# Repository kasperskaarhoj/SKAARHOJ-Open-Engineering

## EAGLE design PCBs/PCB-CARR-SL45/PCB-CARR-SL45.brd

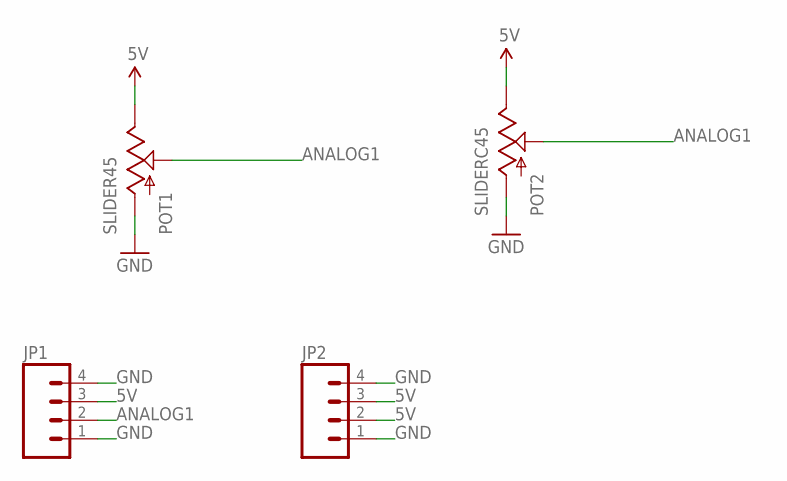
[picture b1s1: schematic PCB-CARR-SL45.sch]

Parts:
JP1, JP2: M04PTH; 1X04
POT1: SLIDER45
POT2: SLIDERC45; SLIDER45-CAR1

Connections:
5V: JP1.3, JP2.2, JP2.3, POT1.1 (E), POT2.1 (E)
ANALOG1: JP1.2, POT1.2A (S), POT2.2A (S)
GND: JP1.1, JP1.4, JP2.1, JP2.4, POT1.3 (A), POT2.3 (A)

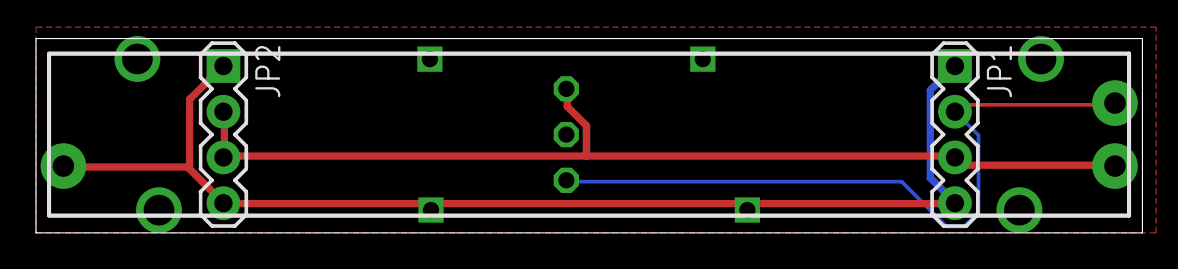
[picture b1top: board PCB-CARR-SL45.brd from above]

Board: 2 copper layers, 61.5 x 10.8 mm, 4 parts (0 on the bottom side), 3 nets.

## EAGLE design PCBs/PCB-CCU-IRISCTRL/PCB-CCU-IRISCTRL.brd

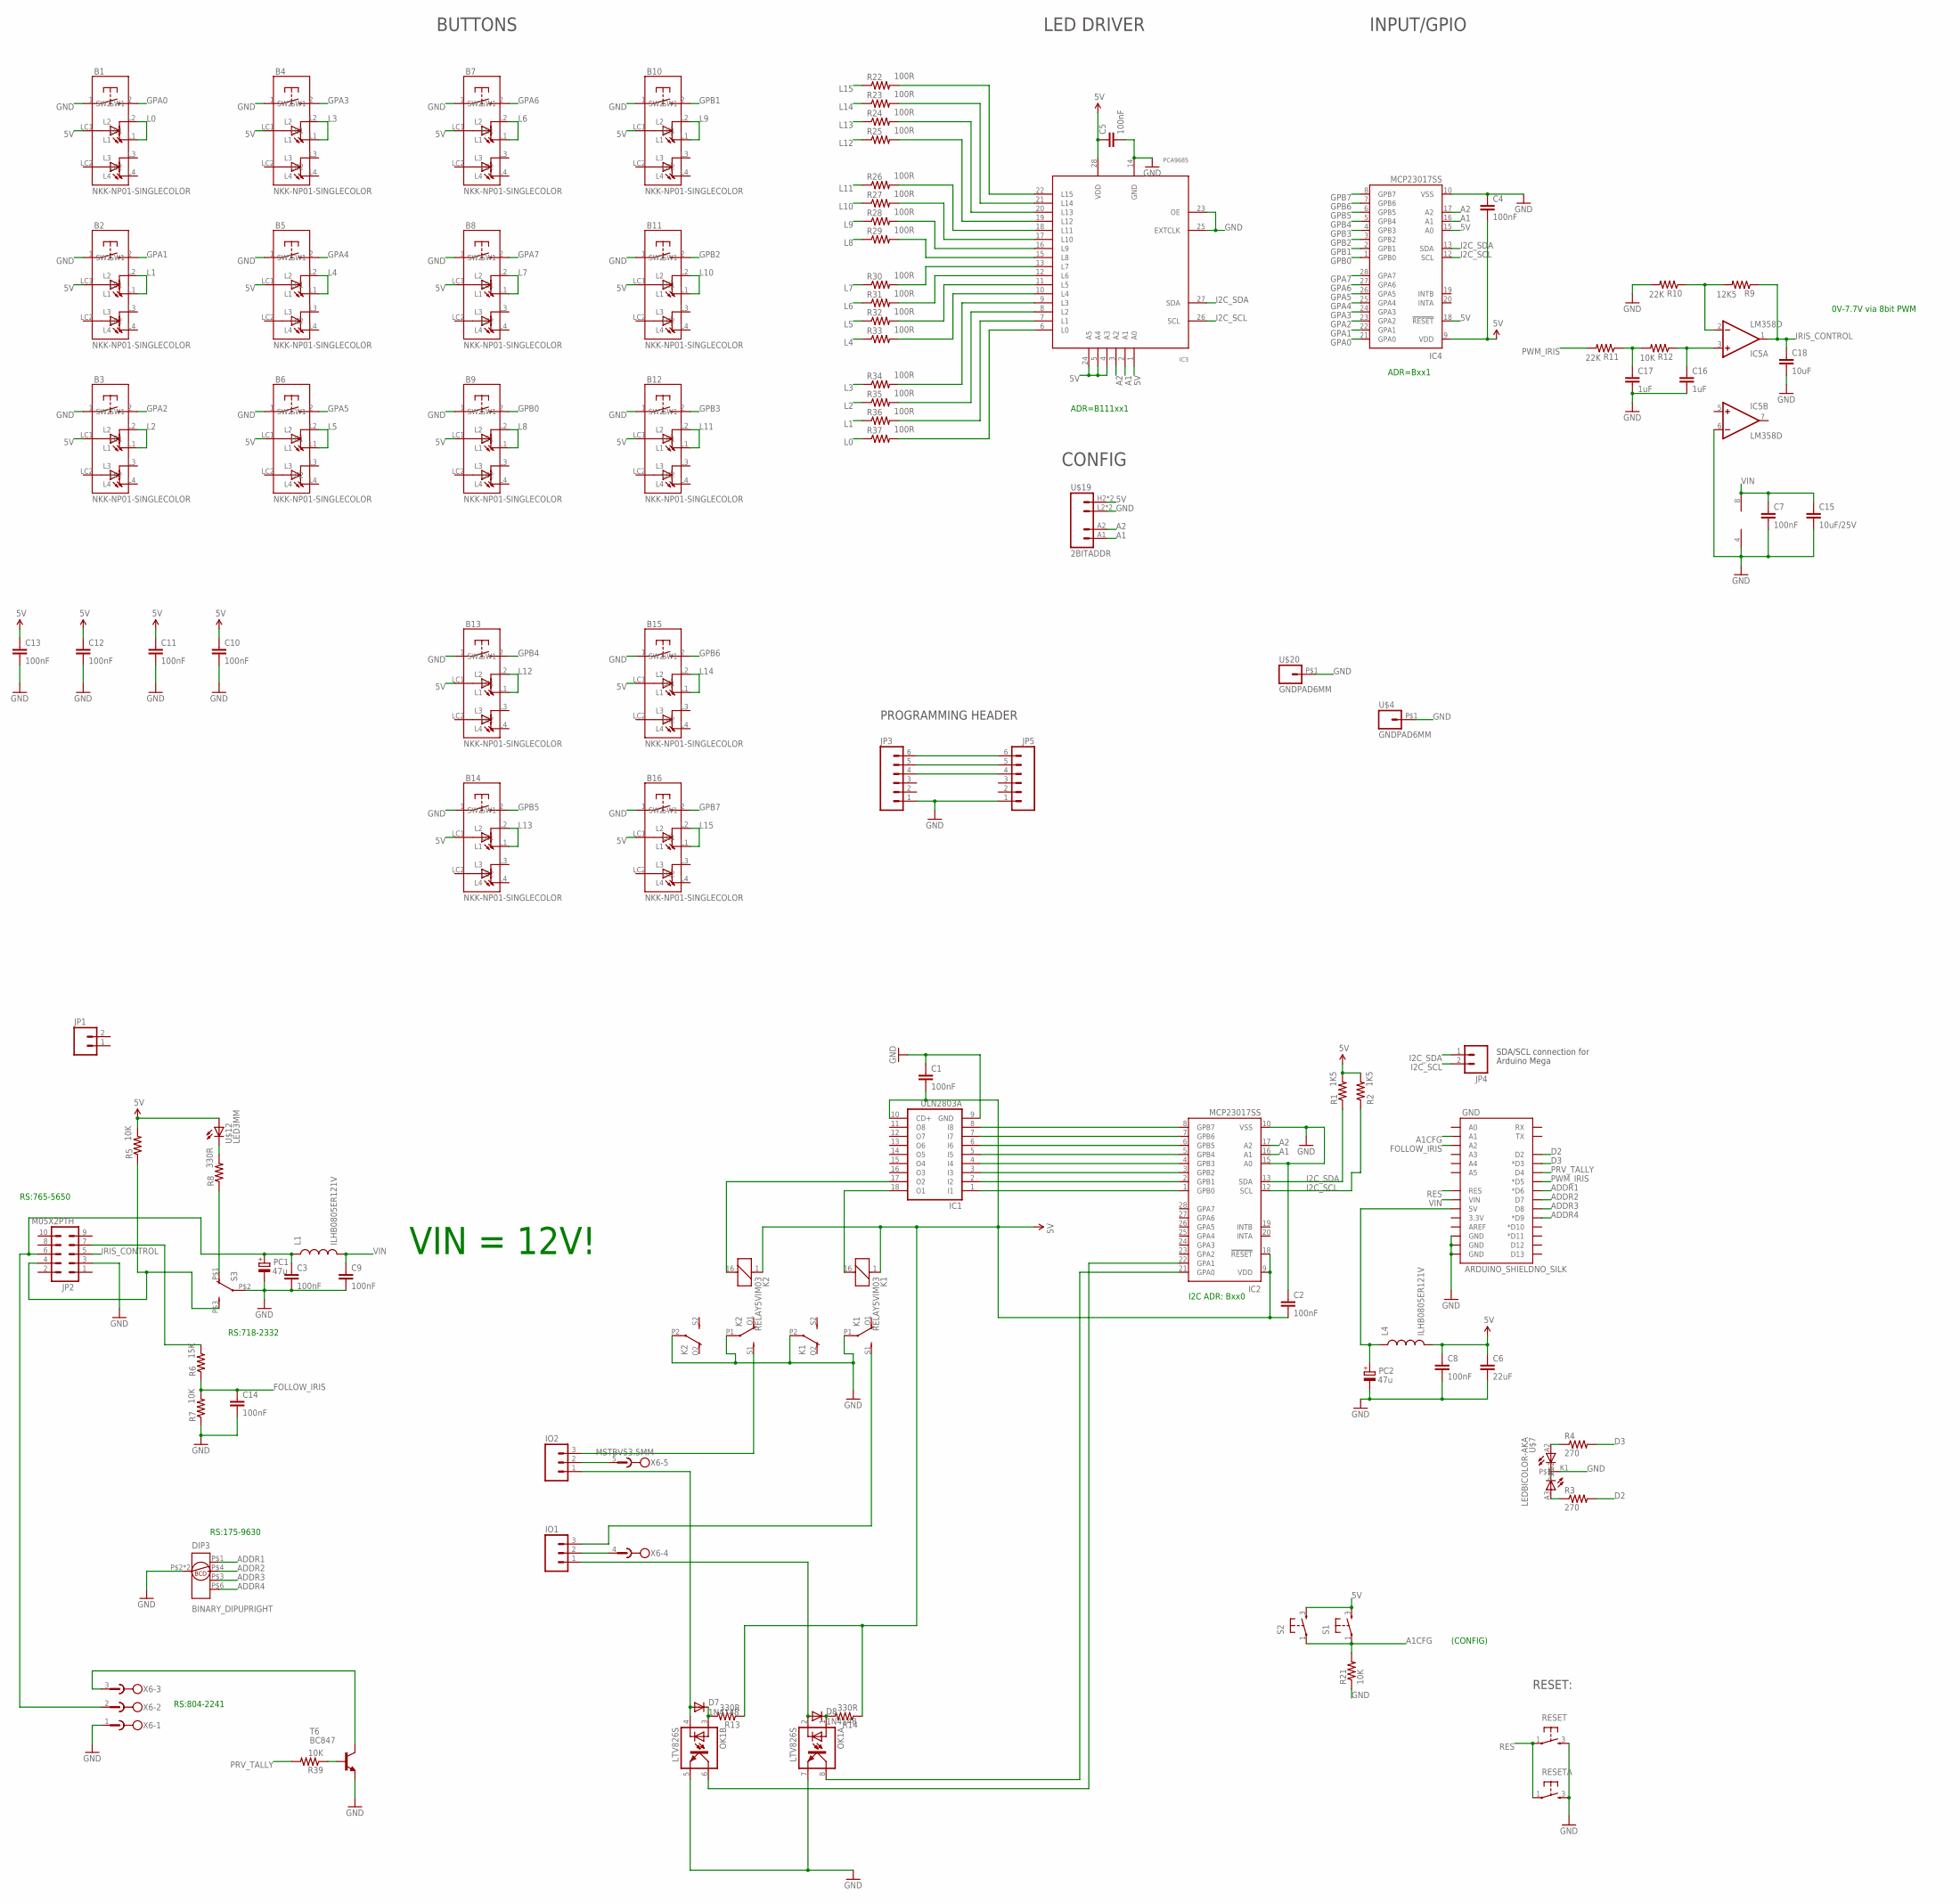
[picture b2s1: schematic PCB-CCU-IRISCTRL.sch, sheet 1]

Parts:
B1, B2, B3, B4, B5, B6, B7, B8, B9, B10, B11, B12, B13, B14, B15, B16: NKK-NP01-SINGLECOLOR; NKK-NP01
C1: 100nF; 0805
C2, C3, C4, C5, C7, C8, C9, C10, C11, C12, C13, C14: 100nF; 0603-CAP
C6: 22uF; 0805
C15: 10uF/25V; 0805
C16, C17: 1uF; 0805
C18: 10uF; 0805
D7, D8: 1N4148; SOD-323
DIP3: BINARY_DIPUPRIGHT; P65SMT_UPRIGHT_TH
GND: ARDUINO_SHIELDNO_SILK; DUEMILANOVE_VIAS
IC1: ULN2803A; SO18W
IC2: MCP23017SS; SSOP28
IC3: PCA9685; TSSOP28
IC4: MCP23017SS; SSOP28; MPN MCP23017-E/SS
IC5: LM358D; SO08
IO1, IO2: M03LOCK; 1X03_LOCK
JP1, JP4: M02PTH; 1X02
JP2: M05X2PTH; AVR_ICSP
JP3, JP5: M06POLAR; MOLEX-1X6
K1, K2: RELAY5VIM03; DS2Y
L1, L4: ILHB0805ER121V; 0805
OK1: LTV826S; DIL8-SMD
PC1, PC2: 47u; PANASONIC_D
R1, R2: 1K5; 0603-RES
R3, R4: 270; 0603-RES
R5, R7, R12, R21, R39: 10K; 0603-RES
R6: 15K; 0603-RES
R8, R13, R14: 330R; 0603-RES
R9: 12K5; 0603-RES
R10, R11: 22K; 0603-RES
R22, R23, R24, R25, R26, R27, R28, R29, R30, R31, R32, R33, R34, R35, R36, R37: 100R; 0603-RES
RESET: TAC_SWITCH; PUSHBUTTON
RESETA: TAC_SWITCH; PUSHBUTTON
S1, S2: TAC_SWITCH; PUSHBUTTON
S3: SWITCH-DPST; TECONNECTIVITY-DPST
T6: BC847; SOT23
U$4, U$20: GNDPAD6MM; 3.2MMPAD6MM
U$7: LEDBICOLOR-AKA; LED5MM-BICOLOR
U$12: LED3MM
U$19: 2BITADDR
X6: MSTBV53.5MM; MSTBV5-3.5

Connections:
5V: B1.LC1, B2.LC1, B3.LC1, B4.LC1, B5.LC1, B6.LC1, B7.LC1, B8.LC1, B9.LC1, B10.LC1, B11.LC1, B12.LC1, B13.LC1, B14.LC1, B15.LC1, B16.LC1, C1.2, C2.2, C4.2, C5.1, C6.1, C8.1, C10.1, C11.1, C12.1, C13.1, IC1.10 (CD+), IC2.9 (VDD), IC2.18 (!RESET), IC3.1 (A0), IC3.4 (A3), IC3.5 (A4), IC3.24 (A5), IC3.28 (VDD), IC4.9 (VDD), IC4.15 (A0), IC4.18 (!RESET), K1.1, K2.1, L4.2, R1.2, R2.2, R5.2, R13.1, R14.1, S1.3, S2.3, U$12.A, U$19.H2 (VCC), U$19.H3 (VCC)
A1: IC2.16 (A1), IC3.2 (A1), IC4.16 (A1), U$19.A1
A1CFG: GND.A1, R21.2, S1.1, S2.1
A2: IC2.17 (A2), IC3.3 (A2), IC4.17 (A2), U$19.A2
ADDR1: DIP3.P$1 (1), GND.D6 (*D6)
ADDR2: DIP3.P$4 (2), GND.D7
ADDR3: DIP3.P$3 (4), GND.D8
ADDR4: DIP3.P$6 (8), GND.D9 (*D9)
ARD_5V: GND.5V, L4.1, PC2.+
D2: GND.D2, R3.2
D3: GND.D3 (*D3), R4.2
FOLLOW_IRIS: C14.1, GND.A2, R6.1, R7.2
GND: B1.1 (SW1), B2.1 (SW1), B3.1 (SW1), B4.1 (SW1), B5.1 (SW1), B6.1 (SW1), B7.1 (SW1), B8.1 (SW1), B9.1 (SW1), B10.1 (SW1), B11.1 (SW1), B12.1 (SW1), B13.1 (SW1), B14.1 (SW1), B15.1 (SW1), B16.1 (SW1), C1.1, C2.1, C3.2, C4.1, C5.2, C6.2, C7.2, C8.2, C9.2, C10.2, C11.2, C12.2, C13.2, C14.2, C15.2, C16.2, C17.2, C18.2, DIP3.P$2 (GND), DIP3.P$5 (GND), GND.GND@0 (GND), GND.GND@1 (GND), GND.GND@2 (GND), IC1.9 (GND), IC2.10 (VSS), IC2.15 (A0), IC3.14 (GND), IC3.23 (OE), IC3.25 (EXTCLK), IC4.10 (VSS), IC5.4 (V-), IC5.6 (-IN), JP2.3, JP3.1, JP5.1, K1.P1, K1.P2, K2.P1, K2.P2, OK1.5 (EMIT), OK1.7 (EMIT), PC1.-, PC2.-, R7.1, R10.2, R21.1, RESET.3, RESETA.3, S3.P$2, T6.2 (E), U$4.P$1, U$7.K1, U$19.L2 (GND), U$19.L3 (GND), U$20.P$1, X6.1
GPA0: B1.2 (SW2), IC4.21 (GPA0)
GPA1: B2.2 (SW2), IC4.22 (GPA1)
GPA2: B3.2 (SW2), IC4.23 (GPA2)
GPA3: B4.2 (SW2), IC4.24 (GPA3)
GPA4: B5.2 (SW2), IC4.25 (GPA4)
GPA5: B6.2 (SW2), IC4.26 (GPA5)
GPA6: B7.2 (SW2), IC4.27 (GPA6)
GPA7: B8.2 (SW2), IC4.28 (GPA7)
GPB0: B9.2 (SW2), IC4.1 (GPB0)
GPB1: B10.2 (SW2), IC4.2 (GPB1)
GPB2: B11.2 (SW2), IC4.3 (GPB2)
GPB3: B12.2 (SW2), IC4.4 (GPB3)
GPB4: B13.2 (SW2), IC4.5 (GPB4)
GPB5: B14.2 (SW2), IC4.6 (GPB5)
GPB6: B15.2 (SW2), IC4.7 (GPB6)
GPB7: B16.2 (SW2), IC4.8 (GPB7)
I2C_SCL: IC2.12 (SCL), IC3.26 (SCL), IC4.12 (SCL), JP4.2, R2.1
I2C_SDA: IC2.13 (SDA), IC3.27 (SDA), IC4.13 (SDA), JP4.1, R1.1
IRIS_CONTROL: C18.1, IC5.1 (OUT), JP2.5, R9.1
L0: B1.L1, B1.L2, R37.1
L1: B2.L1, B2.L2, R36.1
L2: B3.L1, B3.L2, R35.1
L3: B4.L1, B4.L2, R34.1
L4: B5.L1, B5.L2, R33.1
L5: B6.L1, B6.L2, R32.1
L6: B7.L1, B7.L2, R31.1
L7: B8.L1, B8.L2, R30.1
L8: B9.L1, B9.L2, R29.1
L9: B10.L1, B10.L2, R28.1
L10: B11.L1, B11.L2, R27.1
L11: B12.L1, B12.L2, R26.1
L12: B13.L1, B13.L2, R25.1
L13: B14.L1, B14.L2, R24.1
L14: B15.L1, B15.L2, R23.1
L15: B16.L1, B16.L2, R22.1
unnamed: IO2.3, K2.S1 (S)
unnamed: IC3.13 (L7), R30.2
unnamed: JP3.4, JP5.4
unnamed: IC1.18 (O1), K1.16 (2)
unnamed: IC1.1 (I1), IC2.1 (GPB0)
unnamed: IO2.2, X6.5
unnamed: R4.1, U$7.A2
unnamed: JP3.5, JP5.5
unnamed: IC1.17 (O2), K2.16 (2)
unnamed: IO1.3, K1.S1 (S)
unnamed: R3.1, U$7.A3
unnamed: IO1.2, X6.4
unnamed: R39.1, T6.1 (B)
unnamed: JP2.7, R6.2
unnamed: R8.1, S3.P$1 (O)
unnamed: C3.1, JP2.6, L1.1, PC1.+, X6.2
unnamed: R8.2, U$12.K (C)
unnamed: C17.1, R11.1, R12.2
unnamed: IC3.12 (L6), R31.2
unnamed: C16.1, IC5.3 (+IN), R12.1
unnamed: IC5.2 (-IN), R9.2, R10.1
unnamed: IC3.11 (L5), R32.2
unnamed: IC3.10 (L4), R33.2
unnamed: IC1.2 (I2), IC2.2 (GPB1)
unnamed: IC1.3 (I3), IC2.3 (GPB2)
unnamed: IC1.4 (I4), IC2.4 (GPB3)
unnamed: IC1.5 (I5), IC2.5 (GPB4)
unnamed: IC1.6 (I6), IC2.6 (GPB5)
unnamed: IC1.7 (I7), IC2.7 (GPB6)
unnamed: IC1.8 (I8), IC2.8 (GPB7)
unnamed: JP3.6, JP5.6
unnamed: D7.1 (C), OK1.3 (A), R13.2
unnamed: D8.1 (C), OK1.1 (A), R14.2
unnamed: D8.2 (A), IO1.1, OK1.2 (C)
unnamed: IC2.21 (GPA0), OK1.8 (COL)
unnamed: IC3.9 (L3), R34.2
unnamed: IC3.8 (L2), R35.2
unnamed: D7.2 (A), IO2.1, OK1.4 (C)
unnamed: IC3.7 (L1), R36.2
unnamed: IC2.22 (GPA1), OK1.6 (COL)
unnamed: IC3.6 (L0), R37.2
unnamed: IC3.15 (L8), R29.2
unnamed: IC3.16 (L9), R28.2
unnamed: IC3.17 (L10), R27.2
unnamed: IC3.18 (L11), R26.2
unnamed: IC3.19 (L12), R25.2
unnamed: IC3.20 (L13), R24.2
unnamed: IC3.21 (L14), R23.2
unnamed: IC3.22 (L15), R22.2
PRV_TALLY: GND.D4, R39.2
PWM_IRIS: GND.D5 (*D5), R11.2
RES: GND.RES, RESET.1, RESETA.1
RESET: T6.3 (C), X6.3
VIN: C7.1, C9.1, C15.1, GND.VIN, IC5.8 (V+), L1.2
_IRIS_MANUAL: JP2.4, R5.1, S3.P$3 (S)

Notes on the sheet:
I2C ADR: Bxx0
SDA/SCL connection for
Arduino Mega
(CONFIG)
ADR=B111xx1
ADR=Bxx1
BUTTONS
LED DRIVER
INPUT/GPIO
CONFIG
RESET:
PROGRAMMING HEADER
VIN = 12V!
RS:175-9630
RS:718-2332
RS:804-2241
RS:765-5650
0V-7.7V via 8bit PWM

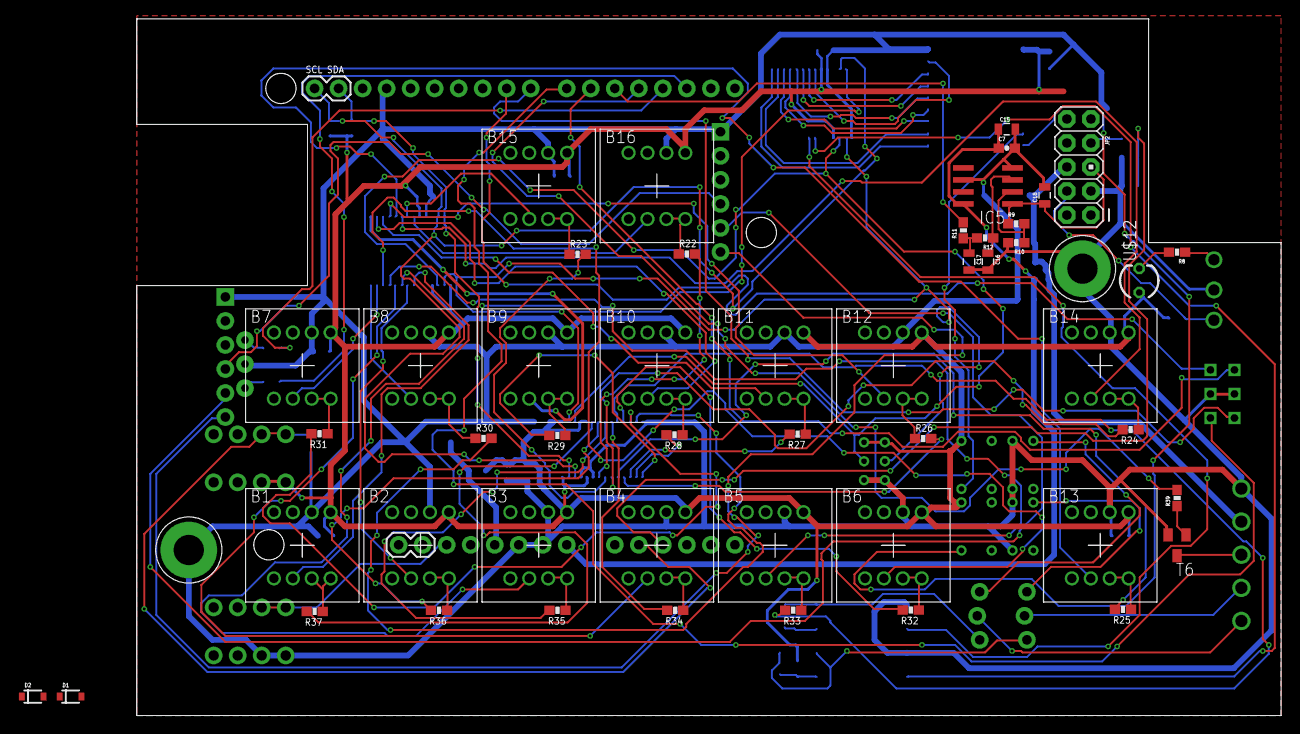
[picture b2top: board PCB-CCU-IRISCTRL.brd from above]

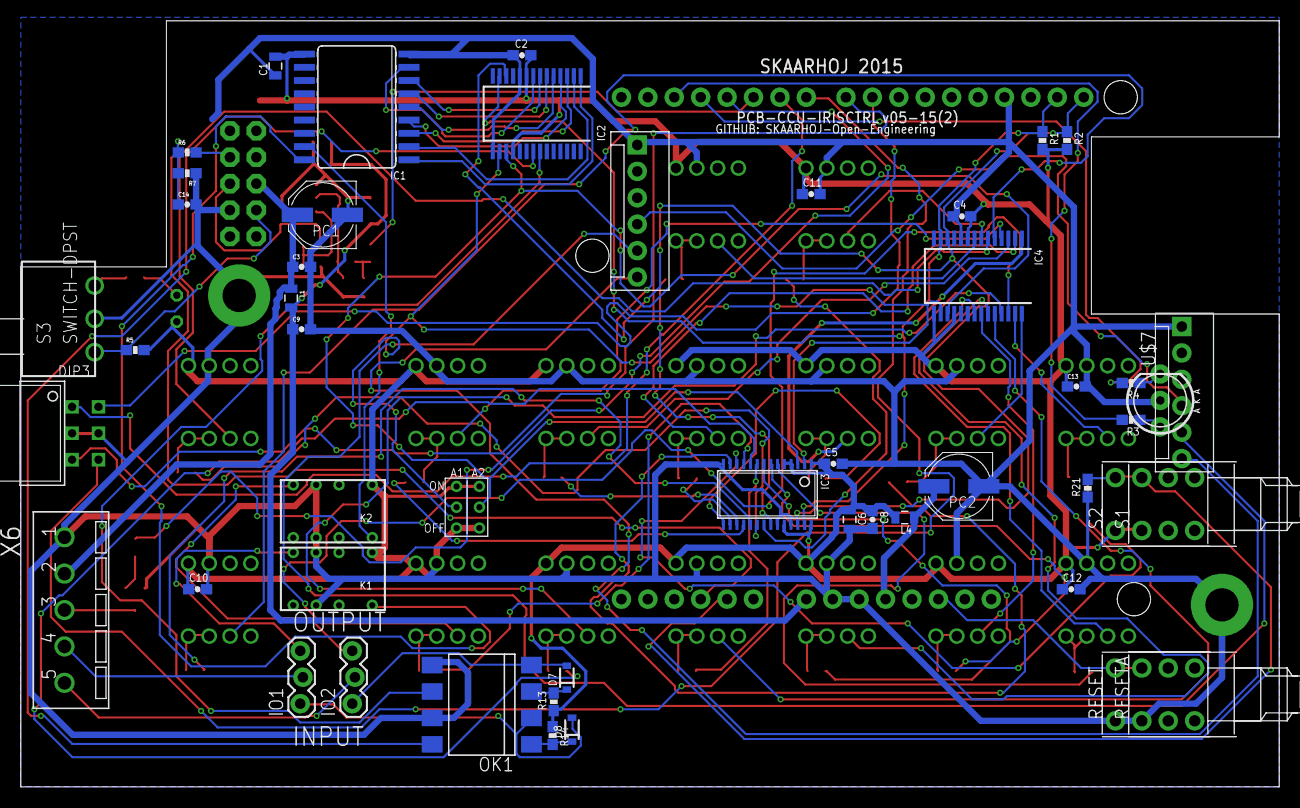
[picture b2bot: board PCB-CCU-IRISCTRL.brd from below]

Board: 2 copper layers, 121.0 x 73.7 mm, 103 parts (49 on the bottom side), 103 nets.

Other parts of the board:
D1, D2: 1N4148; SOD-323

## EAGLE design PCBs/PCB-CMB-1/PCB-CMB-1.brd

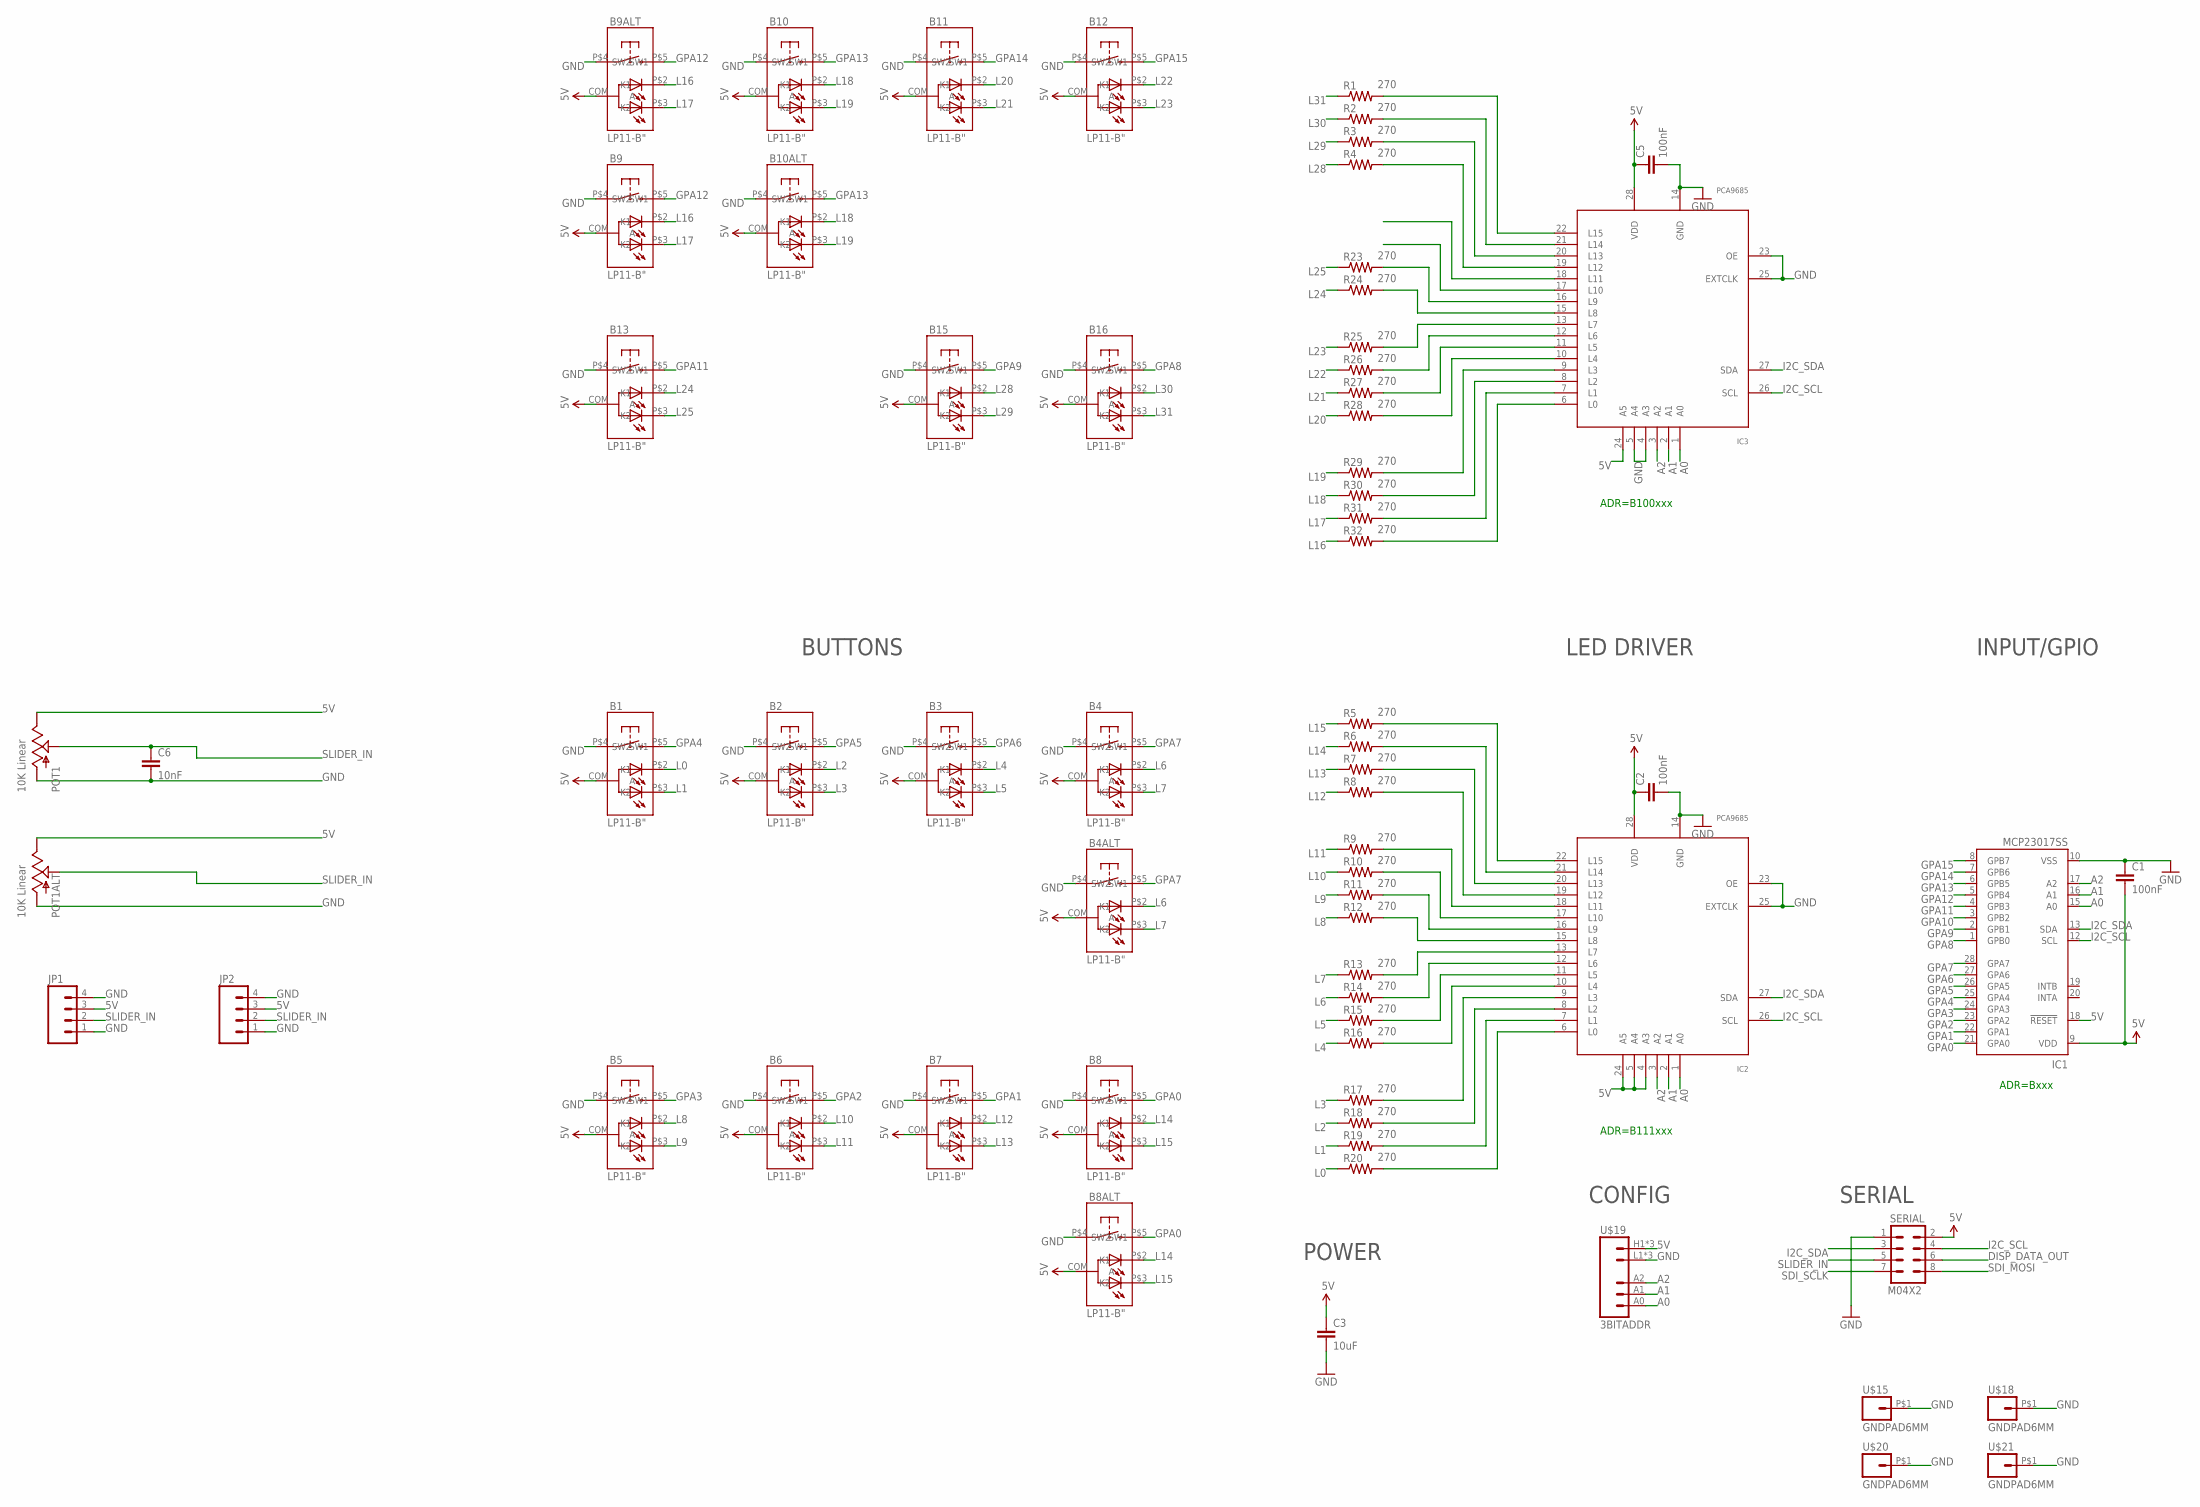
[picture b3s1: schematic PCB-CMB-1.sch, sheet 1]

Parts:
B1, B2, B3, B4, B4ALT, B5, B6, B7, B8, B8ALT, B9, B9ALT, B10, B10ALT, B11, B12, B13, B15, B16: LP11-B"; LP11
C1, C2, C5: 100nF; 0603-CAP
C3: 10uF; 0805
C6: 10nF; 0603-CAP
IC1: MCP23017SS; SSOP28; MPN MCP23017-E/SS
IC2, IC3: PCA9685; TSSOP28
JP1, JP2: M04PTH; 1X04
POT1, POT1ALT: 10K Linear; SLIDER20
R1, R2, R3, R4, R5, R6, R7, R8, R9, R10, R11, R12, R13, R14, R15, R16, R17, R18, R19, R20, R23, R24, R25, R26, R27, R28, R29, R30, R31, R32: 270; 0603-RES
SERIAL: M04X2; 2X4
U$15, U$18, U$20, U$21: GNDPAD6MM; 3.2MMPAD6MM
U$19: 3BITADDR

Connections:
5V: B1.COM (A), B2.COM (A), B3.COM (A), B4.COM (A), B4ALT.COM (A), B5.COM (A), B6.COM (A), B7.COM (A), B8.COM (A), B8ALT.COM (A), B9.COM (A), B9ALT.COM (A), B10.COM (A), B10ALT.COM (A), B11.COM (A), B12.COM (A), B13.COM (A), B15.COM (A), B16.COM (A), C1.2, C2.1, C3.1, C5.1, IC1.9 (VDD), IC1.18 (!RESET), IC2.4 (A3), IC2.5 (A4), IC2.24 (A5), IC2.28 (VDD), IC3.24 (A5), IC3.28 (VDD), JP1.3, JP2.3, POT1.1 (E), POT1ALT.1 (E), SERIAL.2, U$19.H1 (VCC), U$19.H2 (VCC), U$19.H3 (VCC)
A0: IC1.15 (A0), IC2.1 (A0), IC3.1 (A0), U$19.A0
A1: IC1.16 (A1), IC2.2 (A1), IC3.2 (A1), U$19.A1
A2: IC1.17 (A2), IC2.3 (A2), IC3.3 (A2), U$19.A2
DISP_DATA_OUT: SERIAL.6
GND: B1.P$4 (SW1), B2.P$4 (SW1), B3.P$4 (SW1), B4.P$4 (SW1), B4ALT.P$4 (SW1), B5.P$4 (SW1), B6.P$4 (SW1), B7.P$4 (SW1), B8.P$4 (SW1), B8ALT.P$4 (SW1), B9.P$4 (SW1), B9ALT.P$4 (SW1), B10.P$4 (SW1), B10ALT.P$4 (SW1), B11.P$4 (SW1), B12.P$4 (SW1), B13.P$4 (SW1), B15.P$4 (SW1), B16.P$4 (SW1), C1.1, C2.2, C3.2, C5.2, C6.2, IC1.10 (VSS), IC2.14 (GND), IC2.23 (OE), IC2.25 (EXTCLK), IC3.4 (A3), IC3.5 (A4), IC3.14 (GND), IC3.23 (OE), IC3.25 (EXTCLK), JP1.1, JP1.4, JP2.1, JP2.4, POT1.3 (A), POT1ALT.3 (A), SERIAL.1, U$15.P$1, U$18.P$1, U$19.L1 (GND), U$19.L2 (GND), U$19.L3 (GND), U$20.P$1, U$21.P$1
GPA0: B8.P$5 (SW2), B8ALT.P$5 (SW2), IC1.21 (GPA0)
GPA1: B7.P$5 (SW2), IC1.22 (GPA1)
GPA2: B6.P$5 (SW2), IC1.23 (GPA2)
GPA3: B5.P$5 (SW2), IC1.24 (GPA3)
GPA4: B1.P$5 (SW2), IC1.25 (GPA4)
GPA5: B2.P$5 (SW2), IC1.26 (GPA5)
GPA6: B3.P$5 (SW2), IC1.27 (GPA6)
GPA7: B4.P$5 (SW2), B4ALT.P$5 (SW2), IC1.28 (GPA7)
GPA8: B16.P$5 (SW2), IC1.1 (GPB0)
GPA9: B15.P$5 (SW2), IC1.2 (GPB1)
GPA10: IC1.3 (GPB2)
GPA11: B13.P$5 (SW2), IC1.4 (GPB3)
GPA12: B9.P$5 (SW2), B9ALT.P$5 (SW2), IC1.5 (GPB4)
GPA13: B10.P$5 (SW2), B10ALT.P$5 (SW2), IC1.6 (GPB5)
GPA14: B11.P$5 (SW2), IC1.7 (GPB6)
GPA15: B12.P$5 (SW2), IC1.8 (GPB7)
I2C_SCL: IC1.12 (SCL), IC2.26 (SCL), IC3.26 (SCL), SERIAL.4
I2C_SDA: IC1.13 (SDA), IC2.27 (SDA), IC3.27 (SDA), SERIAL.3
L0: B1.P$2 (K1), R20.1
L1: B1.P$3 (K2), R19.1
L2: B2.P$2 (K1), R18.1
L3: B2.P$3 (K2), R17.1
L4: B3.P$2 (K1), R16.1
L5: B3.P$3 (K2), R15.1
L6: B4.P$2 (K1), B4ALT.P$2 (K1), R14.1
L7: B4.P$3 (K2), B4ALT.P$3 (K2), R13.1
L8: B5.P$2 (K1), R12.1
L9: B5.P$3 (K2), R11.1
L10: B6.P$2 (K1), R10.1
L11: B6.P$3 (K2), R9.1
L12: B7.P$2 (K1), R8.1
L13: B7.P$3 (K2), R7.1
L14: B8.P$2 (K1), B8ALT.P$2 (K1), R6.1
L15: B8.P$3 (K2), B8ALT.P$3 (K2), R5.1
L16: B9.P$2 (K1), B9ALT.P$2 (K1), R32.1
L17: B9.P$3 (K2), B9ALT.P$3 (K2), R31.1
L18: B10.P$2 (K1), B10ALT.P$2 (K1), R30.1
L19: B10.P$3 (K2), B10ALT.P$3 (K2), R29.1
L20: B11.P$2 (K1), R28.1
L21: B11.P$3 (K2), R27.1
L22: B12.P$2 (K1), R26.1
L23: B12.P$3 (K2), R25.1
L24: B13.P$2 (K1), R24.1
L25: B13.P$3 (K2), R23.1
L28: B15.P$2 (K1), R4.1
L29: B15.P$3 (K2), R3.1
L30: B16.P$2 (K1), R2.1
L31: B16.P$3 (K2), R1.1
unnamed: IC3.13 (L7), R25.2
unnamed: IC3.12 (L6), R26.2
unnamed: IC3.11 (L5), R27.2
unnamed: IC2.13 (L7), R13.2
unnamed: IC2.12 (L6), R14.2
unnamed: IC3.10 (L4), R28.2
unnamed: IC2.11 (L5), R15.2
unnamed: IC3.9 (L3), R29.2
unnamed: IC2.10 (L4), R16.2
unnamed: IC2.9 (L3), R17.2
unnamed: IC2.8 (L2), R18.2
unnamed: IC2.7 (L1), R19.2
unnamed: IC3.8 (L2), R30.2
unnamed: IC3.7 (L1), R31.2
unnamed: IC3.6 (L0), R32.2
unnamed: IC3.15 (L8), R24.2
unnamed: IC3.16 (L9), R23.2
unnamed: IC2.6 (L0), R20.2
unnamed: IC2.15 (L8), R12.2
unnamed: IC2.16 (L9), R11.2
unnamed: IC2.17 (L10), R10.2
unnamed: IC2.18 (L11), R9.2
unnamed: IC2.19 (L12), R8.2
unnamed: IC2.20 (L13), R7.2
unnamed: IC2.21 (L14), R6.2
unnamed: IC2.22 (L15), R5.2
unnamed: IC3.19 (L12), R4.2
unnamed: IC3.20 (L13), R3.2
unnamed: IC3.21 (L14), R2.2
unnamed: IC3.22 (L15), R1.2
SDI_MOSI: SERIAL.8
SDI_SCLK: SERIAL.7
SLIDER_IN: C6.1, JP1.2, JP2.2, POT1.2A (S), POT1ALT.2A (S), SERIAL.5

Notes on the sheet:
ADR=B111xxx
ADR=Bxxx
BUTTONS
LED DRIVER
INPUT/GPIO
POWER
SERIAL
CONFIG
ADR=B100xxx

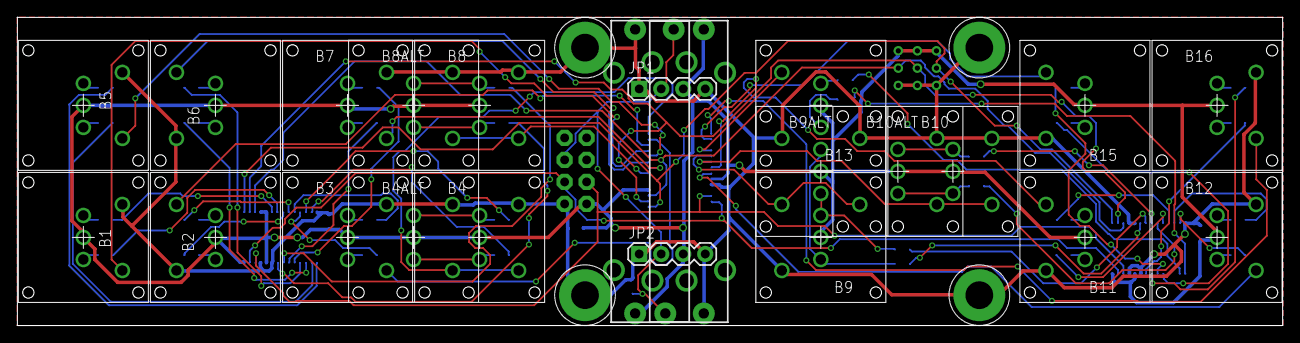
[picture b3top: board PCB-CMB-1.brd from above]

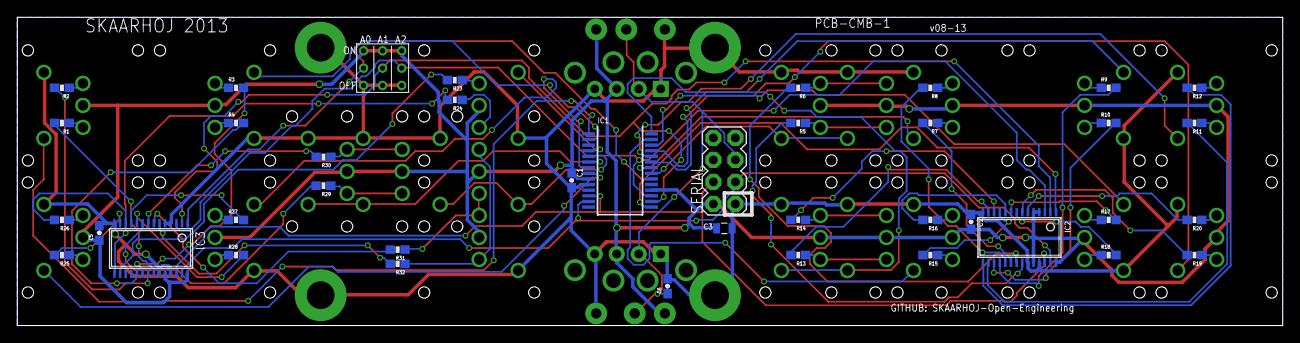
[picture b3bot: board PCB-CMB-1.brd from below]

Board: 2 copper layers, 146.0 x 35.6 mm, 67 parts (40 on the bottom side), 83 nets.

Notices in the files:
parts and their libraries:
SparkFun: Licensing: CC v3.0 Share-Alike You are welcome to use this library for commercial purposes.
